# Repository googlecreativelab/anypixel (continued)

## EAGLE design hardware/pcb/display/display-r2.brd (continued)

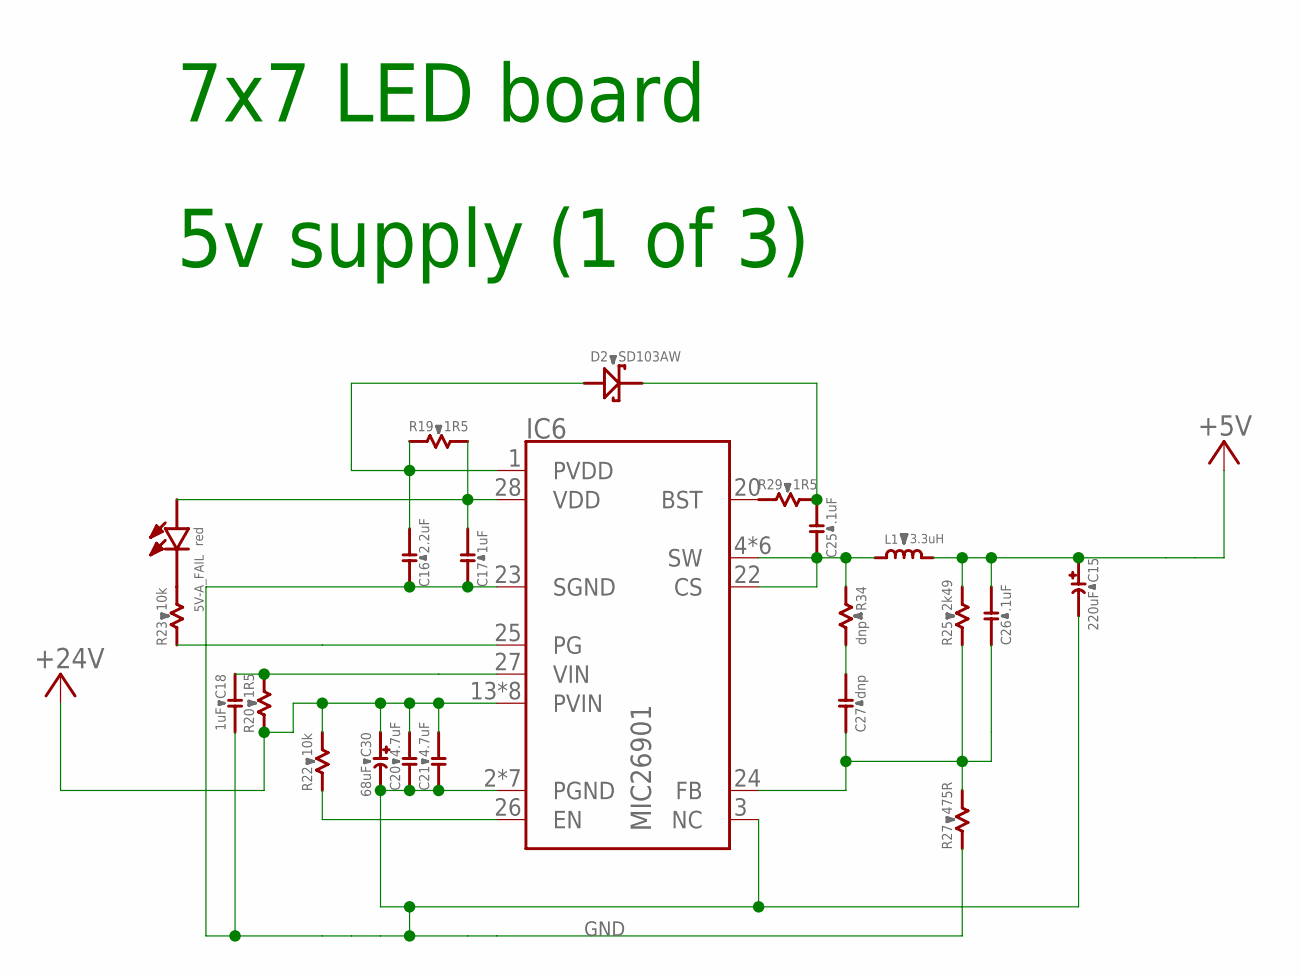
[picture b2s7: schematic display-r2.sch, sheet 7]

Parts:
5V-A_FAIL: red; CHIPLED_0603; PARTNO LTST-C190KRKT
C15: 220uF; E3,5-8; PARTNO 16SEPC220MD
C16: 2.2uF; C0603B; PARTNO C1608X5R1V225K080AC
C17, C18: 1uF; C0603B; PARTNO CGA3E3X5R1H105K080AB
C20, C21: 4.7uF; C1206NT; PARTNO UMK316AB7475KL-T
C25: .1uF; C0603B; PARTNO CGA3E2X7R1H104K080AA
C26: .1uF; C0603B; PARTNO *
C27: dnp; C0603B; PARTNO *
C30: 68uF; E5-10,5; PARTNO PLV1H680MDL1
D2: SD103AW; SOD-323; PARTNO SD103AWS-7-F
IC6: MIC26901; MLF28_5X6; PARTNO MIC26901YJL-TR
L1: 3.3uH; SRP1265A; PARTNO SRP1265A-3R3M
R19, R20, R29: 1R5; R0603B; PARTNO CRCW06031R50FKEA
R22, R23: 10k; R0603B; PARTNO CRCW060310K0FKEA
R25: 2k49; R0603B; PARTNO CRCW06032K49FKEA
R27: 475R; R0603B; PARTNO CRCW0603475RFKEA
R34: dnp; R0603B; PARTNO *

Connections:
+5V: C15.+, C26.2, L1.2, R25.2; also elsewhere on the board
+24V: C20.2, C21.2, C30.+, IC6.13 (PVIN), IC6.14 (PVIN), IC6.15 (PVIN), IC6.16 (PVIN), IC6.17 (PVIN), IC6.18 (PVIN), IC6.19 (PVIN), IC6.PVIN, R20.1, R22.2; also elsewhere on the board
GND: C15.-, C16.1, C17.1, C18.2, C20.1, C21.1, C30.-, IC6.2 (PGND), IC6.3 (NC), IC6.5 (PGND), IC6.6 (PGND), IC6.7 (PGND), IC6.8 (PGND), IC6.21 (PGND), IC6.23 (SGND), IC6.PGND, R27.1; also elsewhere on the board
unnamed: C25.2, D2.C (K), R29.2
unnamed: IC6.25 (PG), R23.1
unnamed: 5V-A_FAIL.C (CATHODE), R23.2
unnamed: C16.2, D2.A, IC6.1 (PVDD), R19.1
unnamed: 5V-A_FAIL.A (ANODE), C17.2, IC6.28 (VDD), R19.2
unnamed: C18.1, IC6.27 (VIN), R20.2
unnamed: IC6.26 (EN), R22.1
unnamed: C27.2, R34.2
unnamed: C26.1, C27.1, IC6.24 (FB), R25.1, R27.2
unnamed: IC6.20 (BST), R29.1
SW: C25.1, IC6.4 (SW), IC6.9 (SW), IC6.10 (SW), IC6.11 (SW), IC6.12 (SW), IC6.22 (CS), IC6.SW, L1.1, R34.1

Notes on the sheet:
5v supply (1 of 3)
7x7 LED board

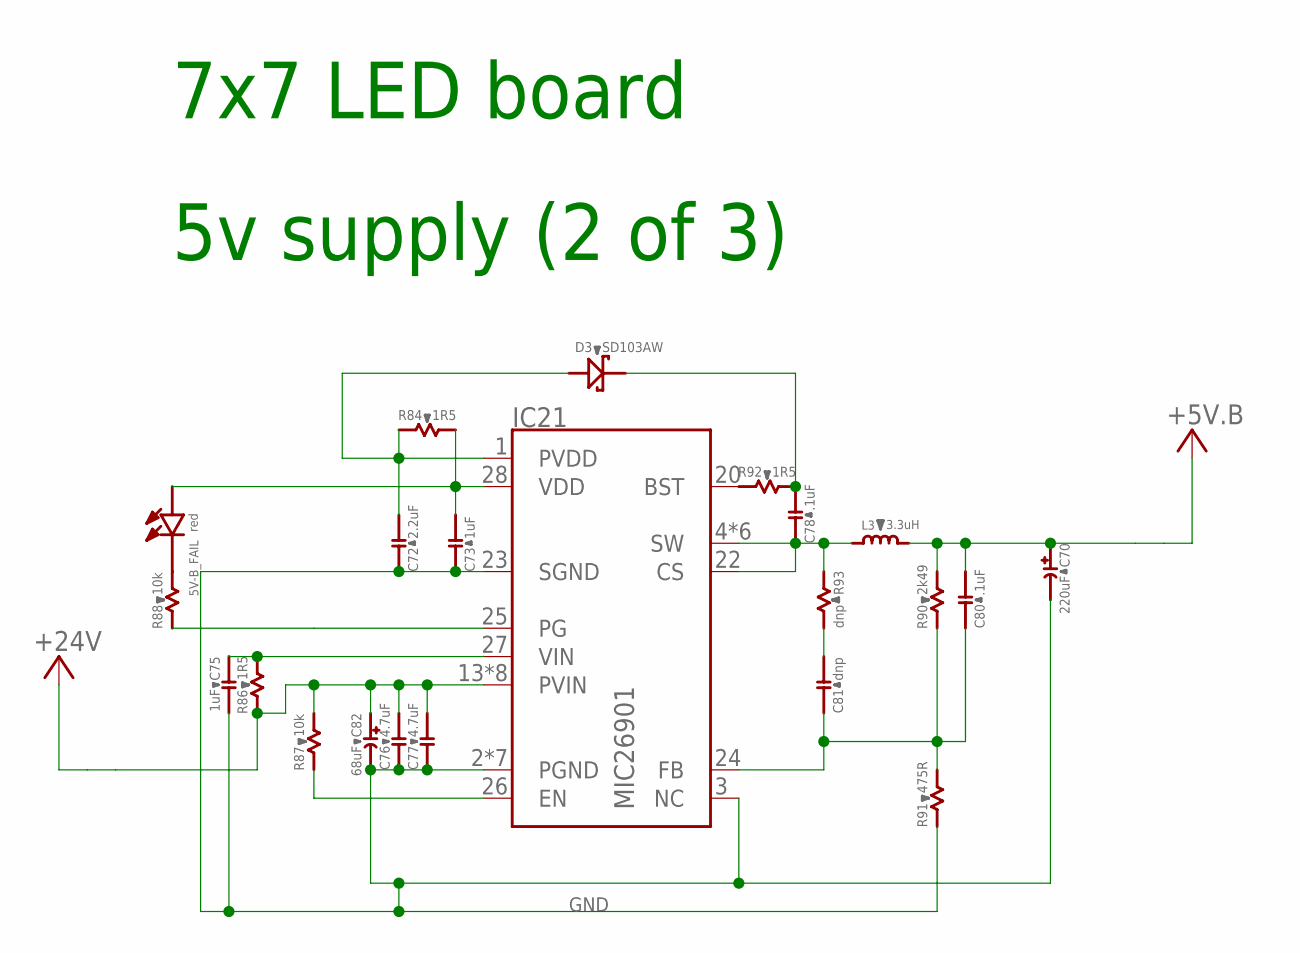
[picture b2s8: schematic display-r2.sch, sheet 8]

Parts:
5V-B_FAIL: red; CHIPLED_0603; PARTNO LTST-C190KRKT
C70: 220uF; E3,5-8; PARTNO 16SEPC220MD
C72: 2.2uF; C0603B; PARTNO C1608X5R1V225K080AC
C73, C75: 1uF; C0603B; PARTNO CGA3E3X5R1H105K080AB
C76, C77: 4.7uF; C1206NT; PARTNO UMK316AB7475KL-T
C78: .1uF; C0603B; PARTNO CGA3E2X7R1H104K080AA
C80: .1uF; C0603B; PARTNO *
C81: dnp; C0603B; PARTNO *
C82: 68uF; E5-10,5; PARTNO PLV1H680MDL1
D3: SD103AW; SOD-323; PARTNO SD103AWS-7-F
IC21: MIC26901; MLF28_5X6; PARTNO MIC26901YJL-TR
L3: 3.3uH; SRP1265A; PARTNO SRP1265A-3R3M
R84, R86, R92: 1R5; R0603B; PARTNO CRCW06031R50FKEA
R87, R88: 10k; R0603B; PARTNO CRCW060310K0FKEA
R90: 2k49; R0603B; PARTNO CRCW06032K49FKEA
R91: 475R; R0603B; PARTNO CRCW0603475RFKEA
R93: dnp; R0603B; PARTNO *

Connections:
+5VB: C70.+, C80.2, L3.2, R90.2; also elsewhere on the board
+24V: C76.2, C77.2, C82.+, IC21.13 (PVIN), IC21.14 (PVIN), IC21.15 (PVIN), IC21.16 (PVIN), IC21.17 (PVIN), IC21.18 (PVIN), IC21.19 (PVIN), IC21.PVIN, R86.1, R87.2; also elsewhere on the board
GND: C70.-, C72.1, C73.1, C75.2, C76.1, C77.1, C82.-, IC21.2 (PGND), IC21.3 (NC), IC21.5 (PGND), IC21.6 (PGND), IC21.7 (PGND), IC21.8 (PGND), IC21.21 (PGND), IC21.23 (SGND), IC21.PGND, R91.1; also elsewhere on the board
unnamed: C78.2, D3.C (K), R92.2
unnamed: IC21.25 (PG), R88.1
unnamed: 5V-B_FAIL.C (CATHODE), R88.2
unnamed: C72.2, D3.A, IC21.1 (PVDD), R84.1
unnamed: 5V-B_FAIL.A (ANODE), C73.2, IC21.28 (VDD), R84.2
unnamed: C75.1, IC21.27 (VIN), R86.2
unnamed: IC21.26 (EN), R87.1
unnamed: C81.2, R93.2
unnamed: C80.1, C81.1, IC21.24 (FB), R90.1, R91.2
unnamed: IC21.20 (BST), R92.1
SW1: C78.1, IC21.4 (SW), IC21.9 (SW), IC21.10 (SW), IC21.11 (SW), IC21.12 (SW), IC21.22 (CS), IC21.SW, L3.1, R93.1

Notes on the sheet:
5v supply (2 of 3)
7x7 LED board

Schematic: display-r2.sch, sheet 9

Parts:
5V-C_FAIL: red; CHIPLED_0603; PARTNO LTST-C190KRKT
C19: 68uF; E5-10,5; PARTNO PLV1H680MDL1
C22: dnp; C0603B; PARTNO *
C23: .1uF; C0603B; PARTNO *
C24: .1uF; C0603B; PARTNO CGA3E2X7R1H104K080AA
C28, C29: 4.7uF; C1206NT; PARTNO UMK316AB7475KL-T
C31, C32: 1uF; C0603B; PARTNO CGA3E3X5R1H105K080AB
C33: 2.2uF; C0603B; PARTNO C1608X5R1V225K080AC
C34: 220uF; E3,5-8; PARTNO 16SEPC220MD
D1: SD103AW; SOD-323; PARTNO SD103AWS-7-F
IC7: MIC26901; MLF28_5X6; PARTNO MIC26901YJL-TR
L2: 3.3uH; SRP1265A; PARTNO SRP1265A-3R3M
R21: dnp; R0603B; PARTNO *
R24, R36, R37: 1R5; R0603B; PARTNO CRCW06031R50FKEA
R26: 475R; R0603B; PARTNO CRCW0603475RFKEA
R28: 2k49; R0603B; PARTNO CRCW06032K49FKEA
R31, R33: 10k; R0603B; PARTNO CRCW060310K0FKEA

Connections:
+5VC: C23.2, C34.+, L2.2, R28.2; also elsewhere on the board
+24V: C19.+, C28.2, C29.2, IC7.13 (PVIN), IC7.14 (PVIN), IC7.15 (PVIN), IC7.16 (PVIN), IC7.17 (PVIN), IC7.18 (PVIN), IC7.19 (PVIN), IC7.PVIN, R33.2, R36.1; also elsewhere on the board
GND: C19.-, C28.1, C29.1, C31.2, C32.1, C33.1, C34.-, IC7.2 (PGND), IC7.3 (NC), IC7.5 (PGND), IC7.6 (PGND), IC7.7 (PGND), IC7.8 (PGND), IC7.21 (PGND), IC7.23 (SGND), IC7.PGND, R26.1; also elsewhere on the board
unnamed: C24.2, D1.C (K), R24.2
unnamed: IC7.25 (PG), R31.1
unnamed: 5V-C_FAIL.C (CATHODE), R31.2
unnamed: C33.2, D1.A, IC7.1 (PVDD), R37.1
unnamed: 5V-C_FAIL.A (ANODE), C32.2, IC7.28 (VDD), R37.2
unnamed: C31.1, IC7.27 (VIN), R36.2
unnamed: IC7.26 (EN), R33.1
unnamed: C22.2, R21.2
unnamed: C22.1, C23.1, IC7.24 (FB), R26.2, R28.1
unnamed: IC7.20 (BST), R24.1
SW2: C24.1, IC7.4 (SW), IC7.9 (SW), IC7.10 (SW), IC7.11 (SW), IC7.12 (SW), IC7.22 (CS), IC7.SW, L2.1, R21.1

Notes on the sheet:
5v supply (3 of 3)
7x7 LED board

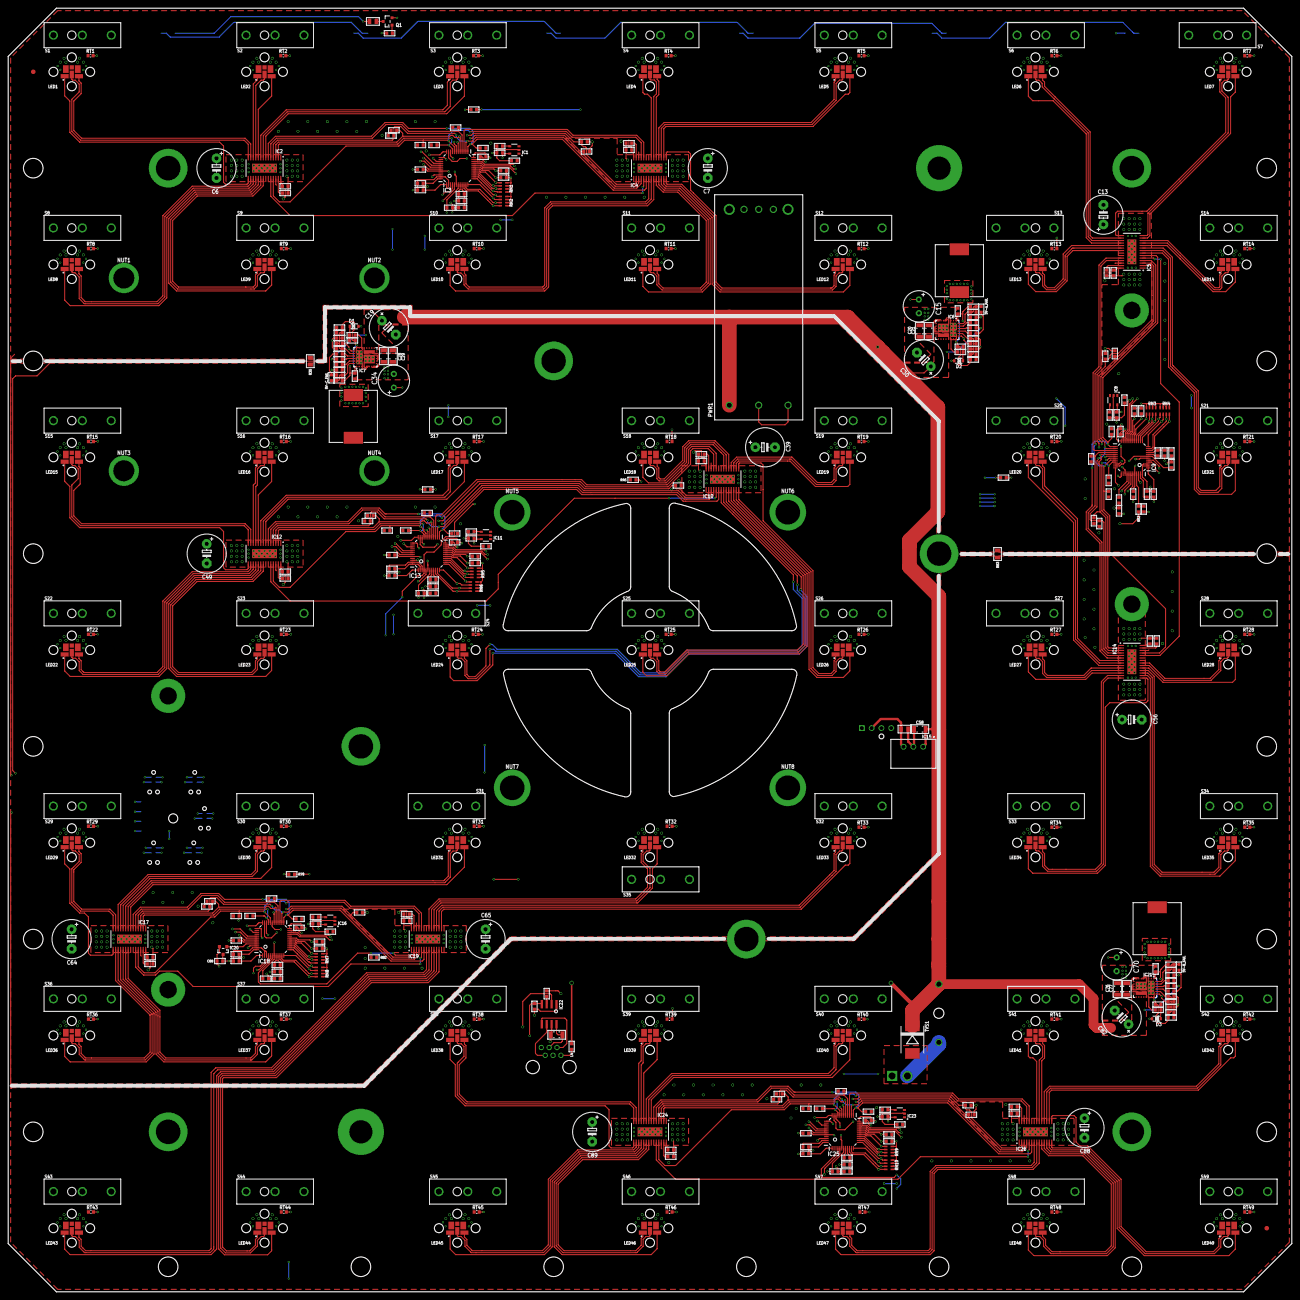
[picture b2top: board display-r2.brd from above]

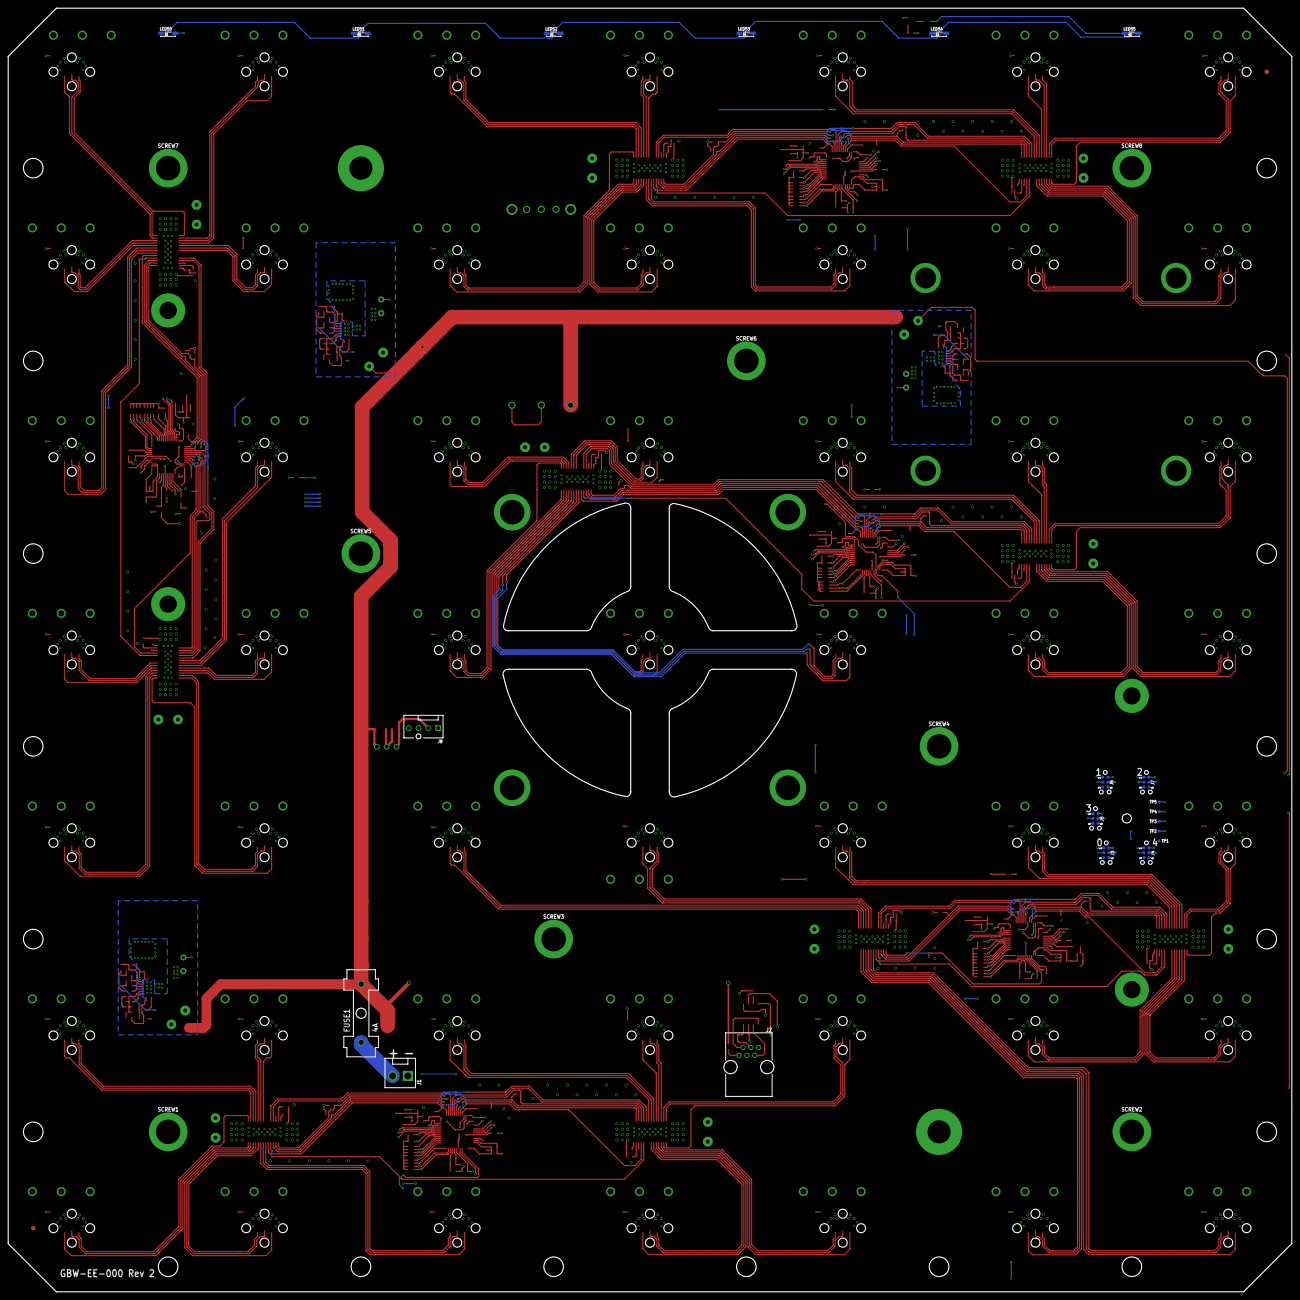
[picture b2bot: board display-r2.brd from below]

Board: 4 copper layers, 333.0 x 333.0 mm, 439 parts (28 on the bottom side), 412 nets.

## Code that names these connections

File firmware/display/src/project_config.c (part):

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    //////////////////// TLC59401 ///////////////////
    /////////////////////////////////////////////////
    const CONFIG_Pin_TypeDef pins_tlc59401[] = {
        { GPIOA, GPIO_Pin_11, GPIO_Speed_Level_2, GPIO_Mode_AF,  GPIO_OType_PP, GPIO_PuPd_NOPULL, GPIO_PinSource11, GPIO_AF_2 },  // GSCLK TIM1.4
        { GPIOB, GPIO_Pin_13, GPIO_Speed_Level_1, GPIO_Mode_AF,  GPIO_OType_PP, GPIO_PuPd_NOPULL, GPIO_PinSource13, GPIO_AF_0 },  // SCK   SPI2
        { GPIOB, GPIO_Pin_15, GPIO_Speed_Level_1, GPIO_Mode_AF,  GPIO_OType_PP, GPIO_PuPd_NOPULL, GPIO_PinSource15, GPIO_AF_0 },  // MOSI  SPI2
        { GPIOB, GPIO_Pin_12, GPIO_Speed_Level_1, GPIO_Mode_OUT, GPIO_OType_PP, GPIO_PuPd_NOPULL, GPIO_PinSource12, 0 },  // MODE
        { GPIOA, GPIO_Pin_8,  GPIO_Speed_Level_1, GPIO_Mode_OUT, GPIO_OType_PP, GPIO_PuPd_NOPULL, GPIO_PinSource8,  0 },  // XLAT
        { GPIOA, GPIO_Pin_12, GPIO_Speed_Level_1, GPIO_Mode_OUT, GPIO_OType_PP, GPIO_PuPd_NOPULL, GPIO_PinSource12, 0 },  // BLANK0
        { GPIOB, GPIO_Pin_14, GPIO_Speed_Level_1, GPIO_Mode_AF,  GPIO_OType_PP, GPIO_PuPd_UP,     GPIO_PinSource14, GPIO_AF_0 },   // MISO  SPI2
        { GPIOF, GPIO_Pin_1,  GPIO_Speed_Level_1, GPIO_Mode_OUT, GPIO_OType_PP, GPIO_PuPd_NOPULL, GPIO_PinSource1,  0 },  // BLANK1
    };
#endif // REV1

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    //////////////////// TLC59401 ///////////////////
    /////////////////////////////////////////////////
    const CONFIG_Pin_TypeDef pins_tlc59401[] = {
        { GPIOA, GPIO_Pin_11, GPIO_Speed_Level_2, GPIO_Mode_AF,  GPIO_OType_PP, GPIO_PuPd_NOPULL, GPIO_PinSource11, GPIO_AF_2 },  // GSCLK TIM1.4
        { GPIOB, GPIO_Pin_13, GPIO_Speed_Level_1, GPIO_Mode_AF,  GPIO_OType_PP, GPIO_PuPd_NOPULL, GPIO_PinSource13, GPIO_AF_0 },  // SCK   SPI2
        { GPIOB, GPIO_Pin_15, GPIO_Speed_Level_1, GPIO_Mode_AF,  GPIO_OType_PP, GPIO_PuPd_NOPULL, GPIO_PinSource15, GPIO_AF_0 },  // MOSI  SPI2
        { GPIOB, GPIO_Pin_12, GPIO_Speed_Level_1, GPIO_Mode_OUT, GPIO_OType_OD, GPIO_PuPd_NOPULL, GPIO_PinSource12, 0 },  // MODE
        { GPIOA, GPIO_Pin_8,  GPIO_Speed_Level_1, GPIO_Mode_OUT, GPIO_OType_OD, GPIO_PuPd_NOPULL, GPIO_PinSource8,  0 },  // XLAT0
        { GPIOA, GPIO_Pin_12, GPIO_Speed_Level_1, GPIO_Mode_OUT, GPIO_OType_OD, GPIO_PuPd_NOPULL, GPIO_PinSource12, 0 },  // BLANK0
        { GPIOB, GPIO_Pin_14, GPIO_Speed_Level_1, GPIO_Mode_AF,  GPIO_OType_PP, GPIO_PuPd_UP,     GPIO_PinSource14, GPIO_AF_0 },   // MISO  SPI2
        { GPIOF, GPIO_Pin_1,  GPIO_Speed_Level_1, GPIO_Mode_OUT, GPIO_OType_OD, GPIO_PuPd_NOPULL, GPIO_PinSource1,  0 },  // BLANK1
        { GPIOF, GPIO_Pin_6,  GPIO_Speed_Level_1, GPIO_Mode_OUT, GPIO_OType_OD, GPIO_PuPd_NOPULL, GPIO_PinSource6,  0 },  // XLAT1
    };

    //FIXME need to add sync pin, although configuration is address dependent since one will have to drive the signal
#endif // REV2

/////////////////////////// BEGIN ITEMS WHICH ARE NOT REVISION SPECIFIC /////////////////////////////////////////
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
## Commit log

2016-06-02 clean commit
2016-06-02 taking the site down temporarily
2016-06-02 Contributors
2016-06-02 launching the site
2016-06-02 added GBW-200 assembly drawing
2016-06-02 added fb cover image
2016-06-02 disable videos on mobile
2016-06-02 smaller captions on mobile
2016-06-02 fixed youtube video resizing on mobile
2016-06-02 removed yt player for mobile
2016-06-02 removed videos temporarily
2016-06-02 changed initial image
2016-06-02 added extra sheet to show the display board assembly procedure
2016-06-03 adds ballpit/app/index.js and makes it an exception in .gitignore
2016-06-03 README.md: add syntax highlighting for code sample
2016-06-03 updating previewer readme to lead users to the examples
2016-06-03 added pdfs for pcb bill of materials
2016-06-03 Added devDependencies in frontend examples
2016-06-05 Consistent punctuation.
2016-06-06 Corrects GPU Gems Ch. 38 Link
2016-06-06 Create LICENSE
2016-06-06 Update LICENSE
2016-06-07 Fix typo
2016-06-07 Add a space
2016-06-08 removed magic number from example code
2016-06-09 updating video locations
2016-06-13 updating media location to google cloud
2016-06-16 website updates
2016-07-08 Updated README.md
    Removed reference deprecated approach
2016-08-01 Update README.md
    Add js syntax highlighting to codeblock
2016-09-05 Pass-through Subtitle
    Ignore pointer events on the subtitle div. This makes the header nice and consistent if you move your cursor over the subtitle so the animation continues to be pretty :grimacing:.
2016-12-23 Fix viewport
2017-01-12 added rpi example
2017-01-12 Update README for rpi-example
2017-01-12 README typo
2017-01-12 Adding Nick Jonas collaborator for rpi-example
2017-02-02 Update color correction in preview.js
    Testing on the wall indicates that this new color correction is more accurate than the previous approach of a simple minimum value threshold of 75%.
2017-02-02 Update color correction in color-emulation.js
    This mirrors the changes made to preview.js
2017-02-02 Remove TODO
    Hopefully the color correction is now accurate enough.
2018-04-14 Revert "Update README.md"
    This reverts commit fa272bcf0eb4295b7189cce9db2a2f9f012bf348.
2018-04-18 Adding a 'flow' example for anypixel frontend.
2018-04-18 Update README.md
    Fix for typo.
2019-11-02 Bump cli from 0.11.3 to 1.0.1 in /frontend/previewer
    Bumps [cli](https://github.com/node-js-libs/cli) from 0.11.3 to 1.0.1.
    - [Release notes](https://github.com/node-js-libs/cli/releases)
    - [Commits](https://github.com/node-js-libs/cli/compare/0.11.3...1.0.1)
